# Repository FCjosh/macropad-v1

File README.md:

# macropad-v1
 Following https://wiki.ai03.com/books/pcb-design/page/pcb-guide-part-1---preparations and using the Archeron library.

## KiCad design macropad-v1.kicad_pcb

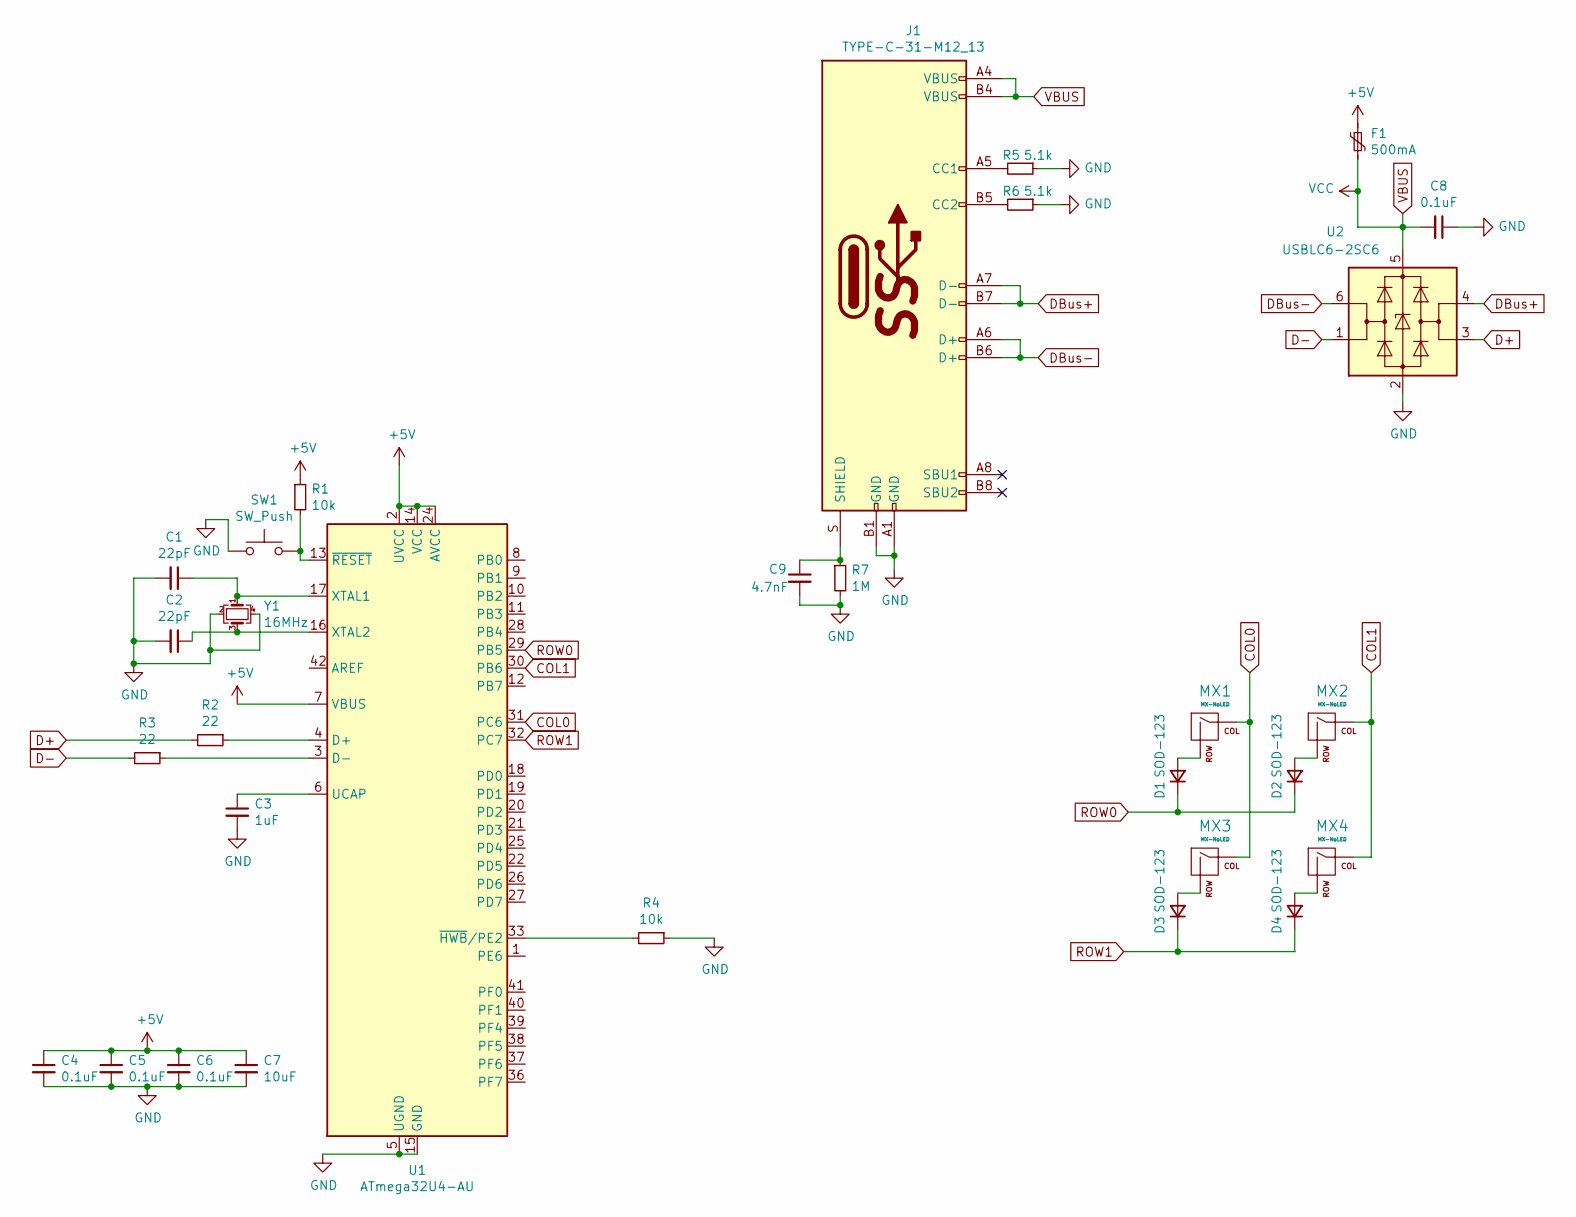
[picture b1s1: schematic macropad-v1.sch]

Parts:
C1, C2: 22pF; C_0805_2012Metric
C3: 1uF; C_0805_2012Metric
C4, C5, C6, C8: 0.1uF; C_0805_2012Metric
C7: 10uF; C_0805_2012Metric
C9: 4.7nF; C_0805_2012Metric
D1, D2, D3, D4: SOD-123; D_SOD-123
F1: 500mA; Fuse_1206_3216Metric
J1: TYPE-C-31-M12_13; TYPE-C-31-M-12
MX1, MX2, MX3, MX4: MX-NoLED; MX-1U-NoLED
R1, R4: 10k; R_0805_2012Metric
R2, R3: 22; R_0805_2012Metric
R5, R6: 5.1k; R_0805_2012Metric
R7: 1M; R_0805_2012Metric
SW1: SW_Push; SKQG-1155865
U1: ATmega32U4-AU; TQFP-44_10x10mm_P0.8mm
U2: USBLC6-2SC6; SOT-23-6
Y1: 16MHz; Crystal_SMD_3225-4Pin_3.2x2.5mm

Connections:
+5V: C4.1, C5.1, C6.1, C7.1, F1.1, R1.1, U1.2 (UVCC), U1.7 (VBUS), U1.14 (VCC), U1.24 (AVCC), U1.34 (VCC), U1.44 (AVCC)
COL0: MX1.1 (COL), MX3.1 (COL), U1.31 (PC6)
COL1: MX2.1 (COL), MX4.1 (COL), U1.30 (PB6)
D+: R2.2, U2.3 (I/O2)
D-: R3.2, U2.1 (I/O1)
DBus+: J1.A7 (D-), J1.B7 (D-), U2.4 (I/O2)
DBus-: J1.A6 (D+), J1.B6 (D+), U2.6 (I/O1)
GND: C1.2, C2.2, C3.2, C4.2, C5.2, C6.2, C7.2, C8.1, C9.2, J1.A1 (GND), J1.B1 (GND), R4.1, R5.1, R6.1, R7.2, SW1.1, U1.5 (UGND), U1.15 (GND), U1.23 (GND), U1.35 (GND), U1.43 (GND), U2.2 (GND), Y1.2, Y1.4
unnamed: C1.1, U1.17 (XTAL1), Y1.1
unnamed: C2.1, U1.16 (XTAL2), Y1.3
unnamed: C3.1, U1.6 (UCAP)
unnamed: C9.1, J1.S (SHIELD), R7.1
unnamed: D1.2 (A), MX1.2 (ROW)
unnamed: D2.2 (A), MX2.2 (ROW)
unnamed: D3.2 (A), MX3.2 (ROW)
unnamed: D4.2 (A), MX4.2 (ROW)
unnamed: J1.A5 (CC1), R5.2
unnamed: J1.B5 (CC2), R6.2
unnamed: R1.2, SW1.2, U1.13 (~RESET)
unnamed: R2.1, U1.4 (D+)
unnamed: R3.1, U1.3 (D-)
unnamed: R4.2, U1.33 (~HWB~/PE2)
ROW0: D1.1 (K), D2.1 (K), U1.29 (PB5)
ROW1: D3.1 (K), D4.1 (K), U1.32 (PC7)
VBUS: C8.2, F1.2, J1.A4 (VBUS), J1.B4 (VBUS), U2.5 (VBUS)

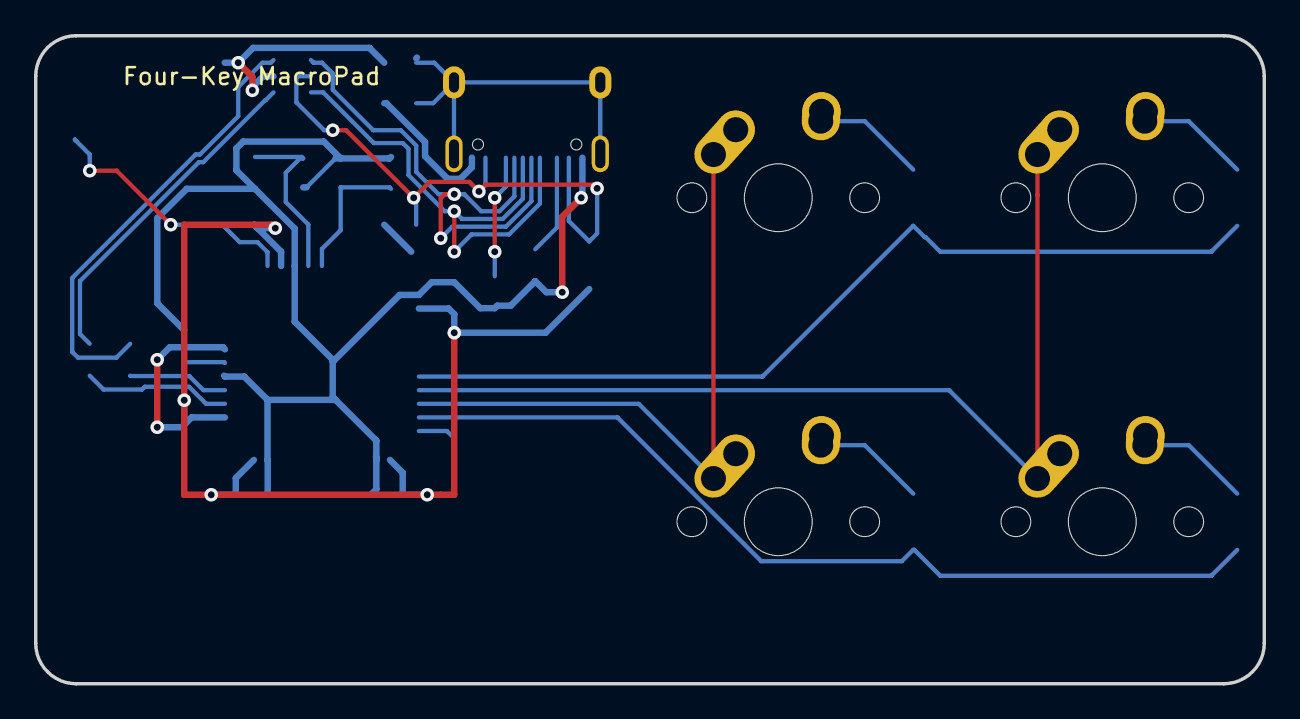
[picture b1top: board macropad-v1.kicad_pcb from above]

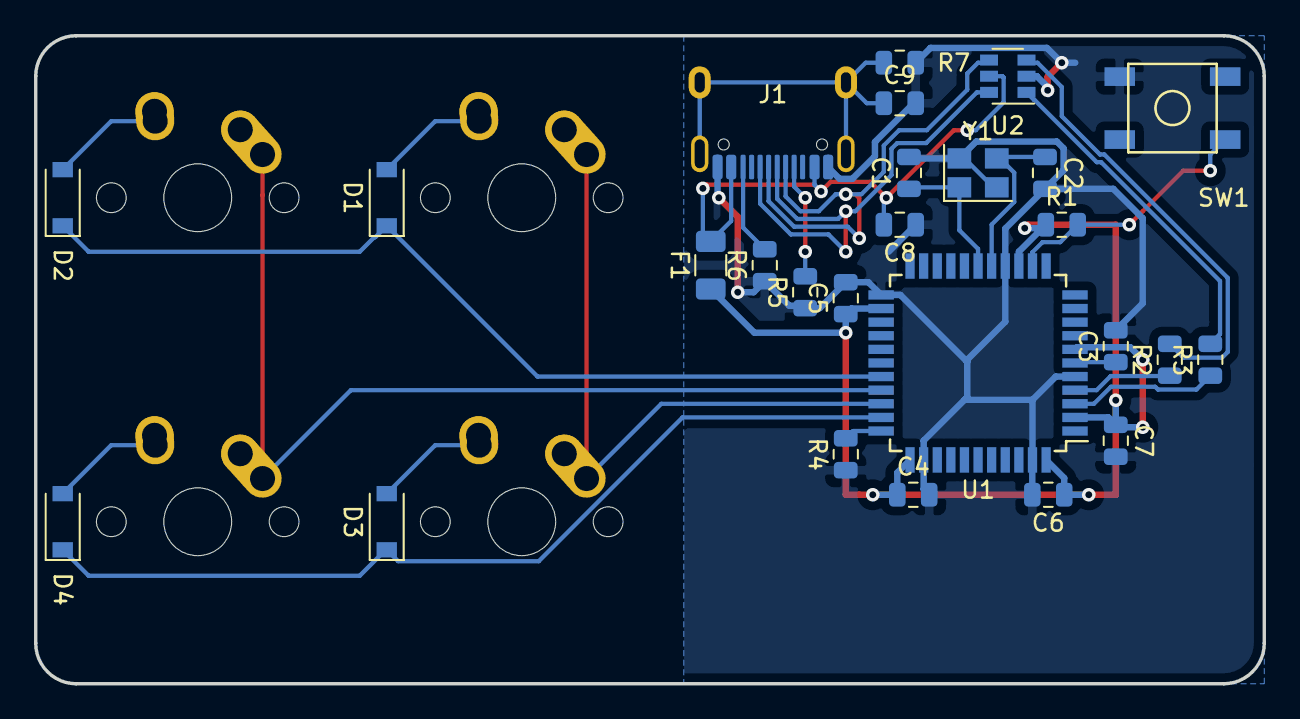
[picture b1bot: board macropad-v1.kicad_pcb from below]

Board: 2 copper layers, 72.2 x 38.1 mm, 30 parts (26 on the bottom side), 25 nets.

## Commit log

2020-08-30 initialize project
2020-08-30 add submodules
2020-08-30 Added footprint and schematic libs
2020-08-30 schematic and footprints
2020-08-30 PCB halfway
2020-08-31 pcb routes
2020-08-31 gerber
2020-09-02 usb c v1
2020-09-03 usb c and better routing
2020-09-03 Update fp-info-cache
